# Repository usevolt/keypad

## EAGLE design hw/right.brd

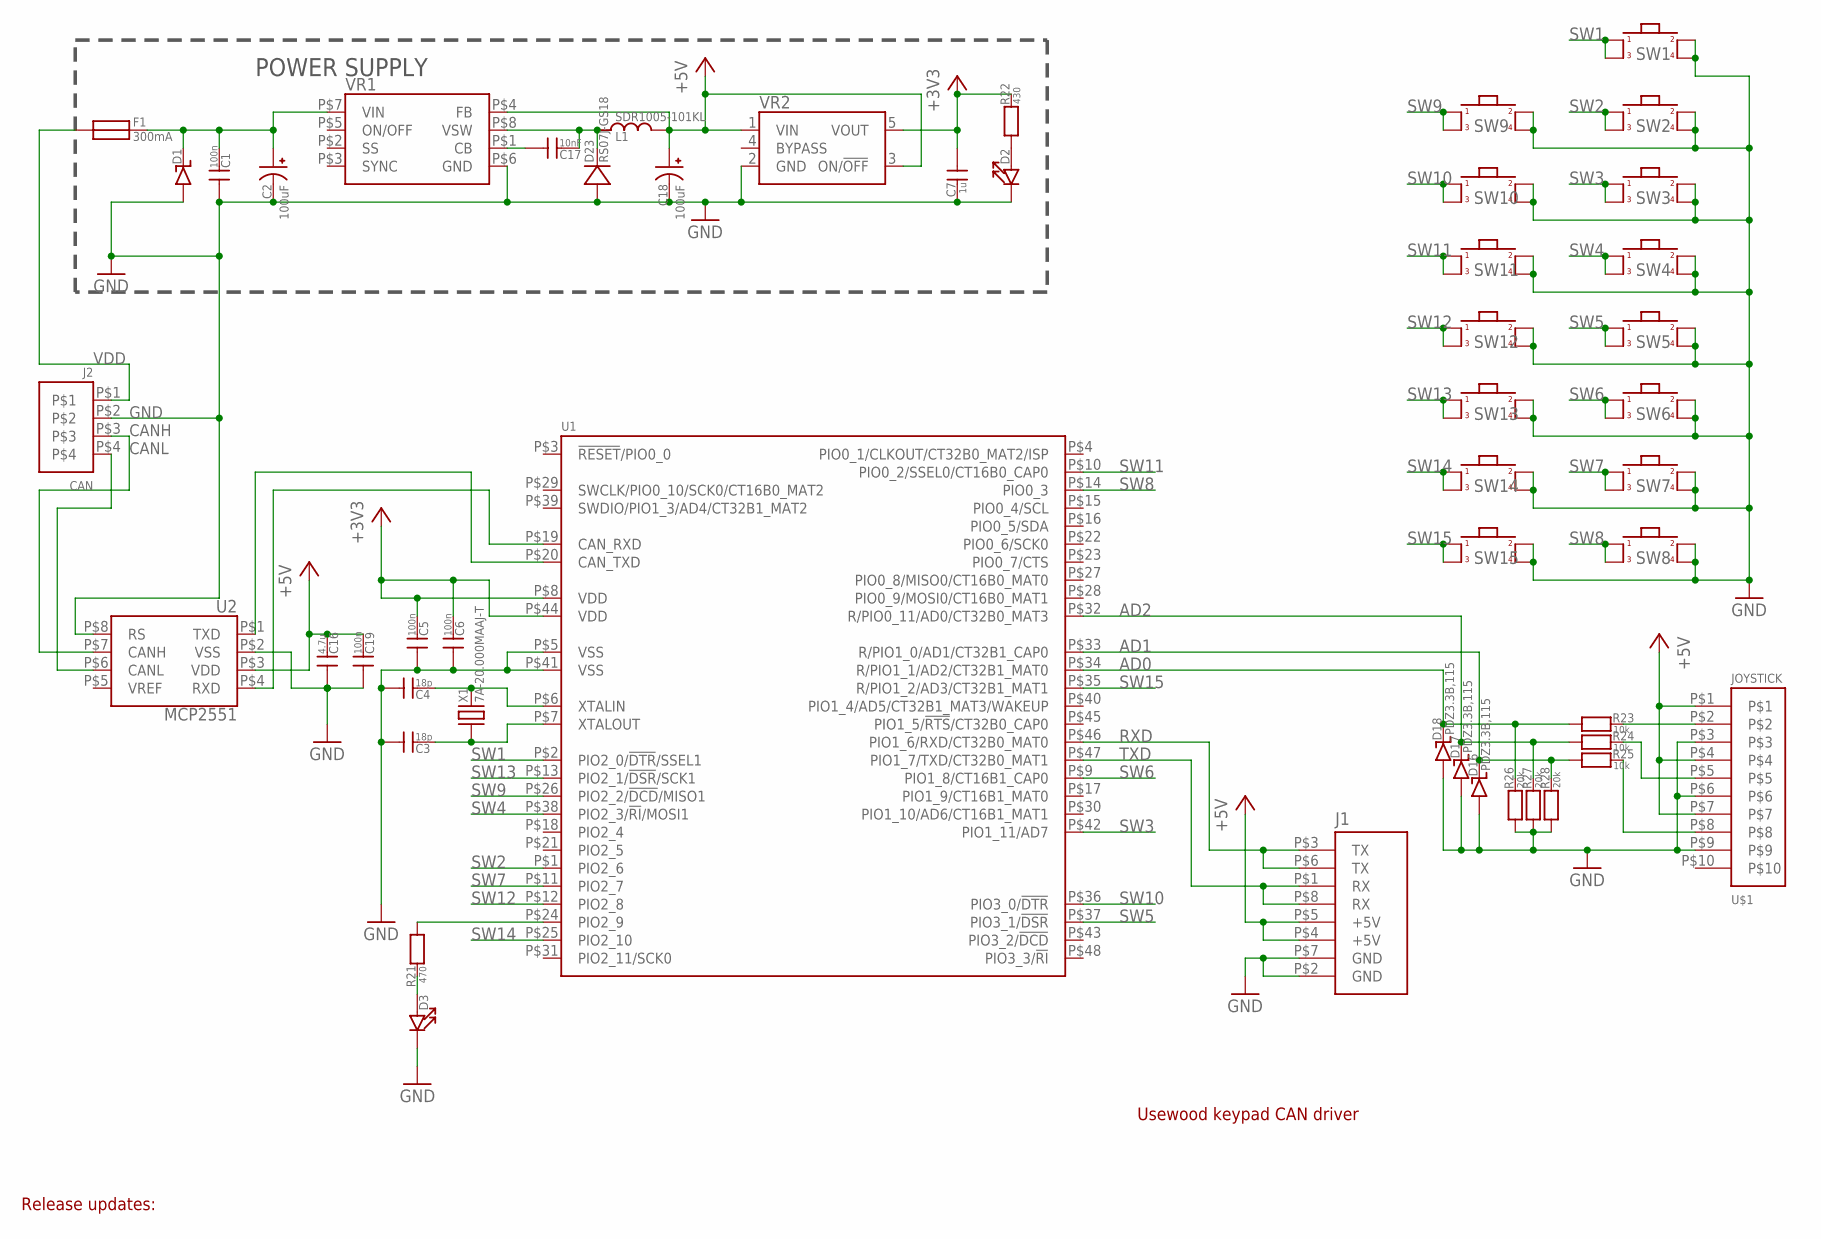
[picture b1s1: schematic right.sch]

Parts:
C1, C5, C6, C19: 100n; 0603_SILKSCREEN
C2, C18: 100uF; CAP_POL_SMD_10X10X10MM
C3, C4: 18p; 0603_SILKSCREEN
C7: 1u; 0603_SILKSCREEN
C16: 4.7u; 0603_SILKSCREEN
C17: 10nF; 0603_SILKSCREEN
D1: DIODE_TVS_SMBJ33A-TRDO-214AA; DO-214AA
D2, D3: LED_0603; 0603_SILKSCREEN
D16, D17, D18: PDZ3.3B,115; SOD123
D23: RS07J-GS18; DO219AB
F1: 300mA; FUSE_100MA
J1: HEADER_USART_2_SMD; HEADER_4_2_SMD
J2: CAN; MOLEX_MICRO_FIT_4WAY_SMD
L1: SDR1005-101KL; INDUCTOR_BOURNS_10X13X5MM
R21: 470; 0603_SILKSCREEN
R22: 430; 0603_SILKSCREEN
R23, R24, R25: 10k; 0603_SILKSCREEN
R26, R27, R28: 20k; 0603_SILKSCREEN
SW1, SW2, SW3, SW4, SW5, SW6, SW7, SW8, SW9, SW10, SW11, SW12, SW13, SW14, SW15: SWITCH_KMR231G; SWITCH_KMR231
U1: LPC11C14_QFP48; QFP48
U2: MCP2551; SOIC8
U$1: JOYSTICK; MOLEX-MICRO-FIT_10WAY
VR1: LM2671SOIC8; SOIC8
VR2: REG_LP2985_SOP5; SOP5
X1: 7A-20.000MAAJ-T; XTAL_SMD_5X3.2

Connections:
+3V3: C5.1, C6.1, C7.0, R22.1, U1.P$8 (VDD), U1.P$44 (VDD), VR2.5 (VOUT)
+5V: C16.1, C18.+, C19.1, J1.P$4 (+5V), J1.P$5 (+5V), L1.P$2, U2.P$3 (VDD), U$1.P$1, U$1.P$4, U$1.P$7, VR1.P$4 (FB), VR2.1 (VIN), VR2.3 (ON/!OFF)
AD0: D18.P$2 (N), R23.0, R26.1, U1.P$34 (R/PIO1_1/AD2/CT32B1_MAT0)
AD1: D16.P$2 (N), R25.0, R28.1, U1.P$33 (R/PIO1_0/AD1/CT32B1_CAP0)
AD2: D17.P$2 (N), R24.0, R27.1, U1.P$32 (R/PIO0_11/AD0/CT32B0_MAT3)
CANH: J2.P$3, U2.P$7 (CANH)
CANL: J2.P$4, U2.P$6 (CANL)
GND: C1.0, C2.-, C3.0, C4.0, C5.0, C6.0, C7.1, C16.0, C18.-, C19.0, D1.P$1, D2.1, D3.1, D16.P$1, D17.P$1, D18.P$1, D23.P$1, J1.P$2 (GND), J1.P$7 (GND), J2.P$2, R26.0, R27.0, R28.0, SW1.P$2, SW1.P$4, SW2.P$2, SW2.P$4, SW3.P$2, SW3.P$4, SW4.P$2, SW4.P$4, SW5.P$2, SW5.P$4, SW6.P$2, SW6.P$4, SW7.P$2, SW7.P$4, SW8.P$2, SW8.P$4, SW9.P$2, SW9.P$4, SW10.P$2, SW10.P$4, SW11.P$2, SW11.P$4, SW12.P$2, SW12.P$4, SW13.P$2, SW13.P$4, SW14.P$2, SW14.P$4, SW15.P$2, SW15.P$4, U1.P$5 (VSS), U1.P$41 (VSS), U2.P$2 (VSS), U2.P$8 (RS), U$1.P$3, U$1.P$6, U$1.P$9, VR1.P$6 (GND), VR2.2 (GND)
LED3: D3.0, R21.1
unnamed: R21.0, U1.P$24 (PIO2_9)
unnamed: D2.0, R22.0
unnamed: C1.1, C2.+, D1.P$2 (N), F1.P$2, VR1.P$7 (VIN)
unnamed: U1.P$20 (CAN_TXD), U2.P$1 (TXD)
unnamed: C17.1, D23.P$2 (N), L1.P$1, VR1.P$8 (VSW)
unnamed: U1.P$19 (CAN_RXD), U2.P$4 (RXD)
unnamed: C17.0, VR1.P$1 (CB)
RXD: J1.P$3 (TX), J1.P$6 (TX), U1.P$46 (PIO1_6/RXD/CT32B0_MAT0)
SW1: SW1.P$1, SW1.P$3, U1.P$2 (PIO2_0/!DTR!/SSEL1)
SW2: SW2.P$1, SW2.P$3, U1.P$1 (PIO2_6)
SW3: SW3.P$1, SW3.P$3, U1.P$42 (PIO1_11/AD7)
SW4: SW4.P$1, SW4.P$3, U1.P$38 (PIO2_3/!RI!/MOSI1)
SW5: SW5.P$1, SW5.P$3, U1.P$37 (PIO3_1/!DSR)
SW6: SW6.P$1, SW6.P$3, U1.P$9 (PIO1_8/CT16B1_CAP0)
SW7: SW7.P$1, SW7.P$3, U1.P$11 (PIO2_7)
SW8: SW8.P$1, SW8.P$3, U1.P$14 (PIO0_3)
SW9: SW9.P$1, SW9.P$3, U1.P$26 (PIO2_2/!DCD!/MISO1)
SW10: SW10.P$1, SW10.P$3, U1.P$36 (PIO3_0/!DTR)
SW11: SW11.P$1, SW11.P$3, U1.P$10 (PIO0_2/SSEL0/CT16B0_CAP0)
SW12: SW12.P$1, SW12.P$3, U1.P$12 (PIO2_8)
SW13: SW13.P$1, SW13.P$3, U1.P$13 (PIO2_1/!DSR!/SCK1)
SW14: SW14.P$1, SW14.P$3, U1.P$25 (PIO2_10)
SW15: SW15.P$1, SW15.P$3, U1.P$35 (R/PIO1_2/AD3/CT32B1_MAT1)
TXD: J1.P$1 (RX), J1.P$8 (RX), U1.P$47 (PIO1_7/TXD/CT32B0_MAT1)
VDD: F1.P$1, J2.P$1
XJOY: R23.1, U$1.P$2
XTALIN: C4.1, U1.P$6 (XTALIN), X1.P$2
XTALOUT: C3.1, U1.P$7 (XTALOUT), X1.P$1
YJOY: R24.1, U$1.P$5
ZJOY: R25.1, U$1.P$8

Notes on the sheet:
Usewood keypad CAN driver
POWER SUPPLY
Release updates:

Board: 2 copper layers, 51 parts (36 on the bottom side), 39 nets, no tracks yet.

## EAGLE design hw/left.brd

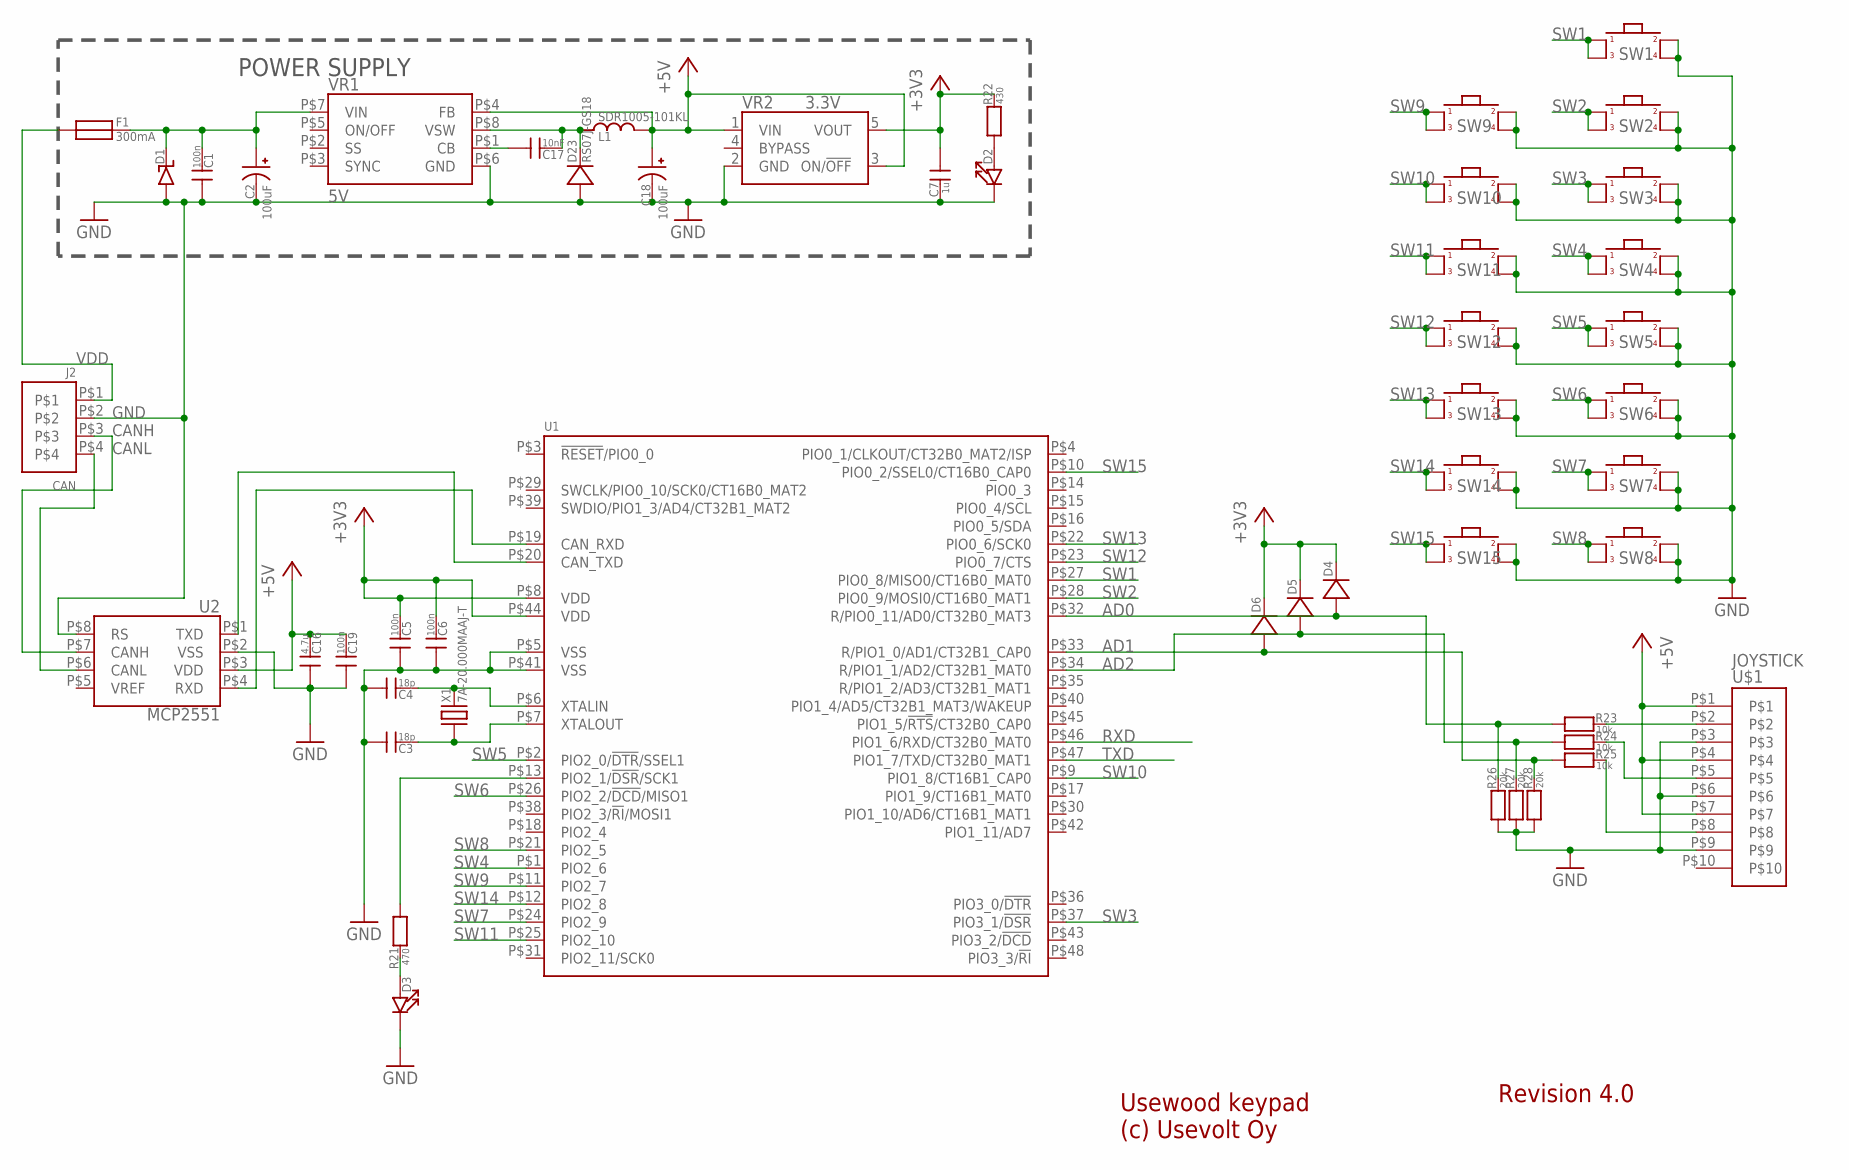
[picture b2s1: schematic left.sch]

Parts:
C1, C5, C6, C19: 100n; 0603_SILKSCREEN
C2, C18: 100uF; CAP_POL_8.3X8.3MM
C3, C4: 18p; 0603_SILKSCREEN
C7: 1u; 0603_SILKSCREEN
C16: 4.7u; 0603_SILKSCREEN
C17: 10nF; 0603_SILKSCREEN
D1: DIODE_TVS_SMBJ33A-TRDO-214AA; DO-214AA
D2, D3: LED_0603; 0603_SILKSCREEN
D4, D5, D6: DIODEDO219AB; DO219AB
D23: RS07J-GS18; DO219AB
F1: 300mA; FUSE_100MA
J2: CAN; MOLEX_MICRO_FIT_4WAY_SMD
L1: SDR1005-101KL; INDUCTOR_BOURNS_10X13X5MM
R21: 470; 0603_SILKSCREEN
R22: 430; 0603_SILKSCREEN
R23, R24, R25: 10k; 0603_SILKSCREEN
R26, R27, R28: 20k; 0603_SILKSCREEN
SW1, SW2, SW3, SW4, SW5, SW6, SW7, SW8, SW9, SW10, SW11, SW12, SW13, SW14, SW15: SWITCH_KSC421J-70SH-LFS
U1: LPC11C14_QFP48; QFP48
U2: MCP2551; SOIC8
U$1: JOYSTICK; MOLEX_MICRO-FIT_10WAY_V
VR1: 5V; SOIC8
VR2: 3.3V; SOP5
X1: 7A-20.000MAAJ-T; XTAL_SMD_5X3.2

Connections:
+3V3: C5.1, C6.1, C7.0, D4.P$2 (N), D5.P$2 (N), D6.P$2 (N), R22.1, U1.P$8 (VDD), U1.P$44 (VDD), VR2.5 (VOUT)
+5V: C16.1, C18.P$2 (+), C19.1, L1.P$2, U2.P$3 (VDD), U$1.P$1, U$1.P$4, U$1.P$7, VR1.P$4 (FB), VR2.1 (VIN), VR2.3 (ON/!OFF)
AD0: D4.P$1, R23.0, R26.1, U1.P$32 (R/PIO0_11/AD0/CT32B0_MAT3)
AD1: D6.P$1, R25.0, R28.1, U1.P$33 (R/PIO1_0/AD1/CT32B1_CAP0)
AD2: D5.P$1, R24.0, R27.1, U1.P$34 (R/PIO1_1/AD2/CT32B1_MAT0)
CANH: J2.P$3, U2.P$7 (CANH)
CANL: J2.P$4, U2.P$6 (CANL)
GND: C1.0, C2.P$1 (-), C3.0, C4.0, C5.0, C6.0, C7.1, C16.0, C18.P$1 (-), C19.0, D1.P$1, D2.1, D3.1, D23.P$1, J2.P$2, R26.0, R27.0, R28.0, SW1.P$3, SW1.P$4, SW2.P$3, SW2.P$4, SW3.P$3, SW3.P$4, SW4.P$3, SW4.P$4, SW5.P$3, SW5.P$4, SW6.P$3, SW6.P$4, SW7.P$3, SW7.P$4, SW8.P$3, SW8.P$4, SW9.P$3, SW9.P$4, SW10.P$3, SW10.P$4, SW11.P$3, SW11.P$4, SW12.P$3, SW12.P$4, SW13.P$3, SW13.P$4, SW14.P$3, SW14.P$4, SW15.P$3, SW15.P$4, U1.P$5 (VSS), U1.P$41 (VSS), U2.P$2 (VSS), U2.P$8 (RS), U$1.P$3, U$1.P$6, U$1.P$9, VR1.P$6 (GND), VR2.2 (GND)
LED3: D3.0, R21.1
unnamed: R21.0, U1.P$13 (PIO2_1/!DSR!/SCK1)
unnamed: D2.0, R22.0
unnamed: C1.1, C2.P$2 (+), D1.P$2 (N), F1.P$2, VR1.P$7 (VIN)
unnamed: U1.P$20 (CAN_TXD), U2.P$1 (TXD)
unnamed: C17.1, D23.P$2 (N), L1.P$1, VR1.P$8 (VSW)
unnamed: U1.P$19 (CAN_RXD), U2.P$4 (RXD)
unnamed: C17.0, VR1.P$1 (CB)
RXD: U1.P$46 (PIO1_6/RXD/CT32B0_MAT0)
SW1: SW1.P$1, SW1.P$2, U1.P$27 (PIO0_8/MISO0/CT16B0_MAT0)
SW2: SW2.P$1, SW2.P$2, U1.P$28 (PIO0_9/MOSI0/CT16B0_MAT1)
SW3: SW3.P$1, SW3.P$2, U1.P$37 (PIO3_1/!DSR)
SW4: SW4.P$1, SW4.P$2, U1.P$1 (PIO2_6)
SW5: SW5.P$1, SW5.P$2, U1.P$2 (PIO2_0/!DTR!/SSEL1)
SW6: SW6.P$1, SW6.P$2, U1.P$26 (PIO2_2/!DCD!/MISO1)
SW7: SW7.P$1, SW7.P$2, U1.P$24 (PIO2_9)
SW8: SW8.P$1, SW8.P$2, U1.P$21 (PIO2_5)
SW9: SW9.P$1, SW9.P$2, U1.P$11 (PIO2_7)
SW10: SW10.P$1, SW10.P$2, U1.P$9 (PIO1_8/CT16B1_CAP0)
SW11: SW11.P$1, SW11.P$2, U1.P$25 (PIO2_10)
SW12: SW12.P$1, SW12.P$2, U1.P$23 (PIO0_7/CTS)
SW13: SW13.P$1, SW13.P$2, U1.P$22 (PIO0_6/SCK0)
SW14: SW14.P$1, SW14.P$2, U1.P$12 (PIO2_8)
SW15: SW15.P$1, SW15.P$2, U1.P$10 (PIO0_2/SSEL0/CT16B0_CAP0)
TXD: U1.P$47 (PIO1_7/TXD/CT32B0_MAT1)
VDD: F1.P$1, J2.P$1
XJOY: R23.1, U$1.P$2
XTALIN: C4.1, U1.P$6 (XTALIN), X1.P$2
XTALOUT: C3.1, U1.P$7 (XTALOUT), X1.P$1
YJOY: R24.1, U$1.P$5
ZJOY: R25.1, U$1.P$8

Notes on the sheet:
Usewood keypad (c) Usevolt Oy
POWER SUPPLY
Revision 4.0

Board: 2 copper layers, 50 parts (1 on the bottom side), 37 nets, no tracks yet.

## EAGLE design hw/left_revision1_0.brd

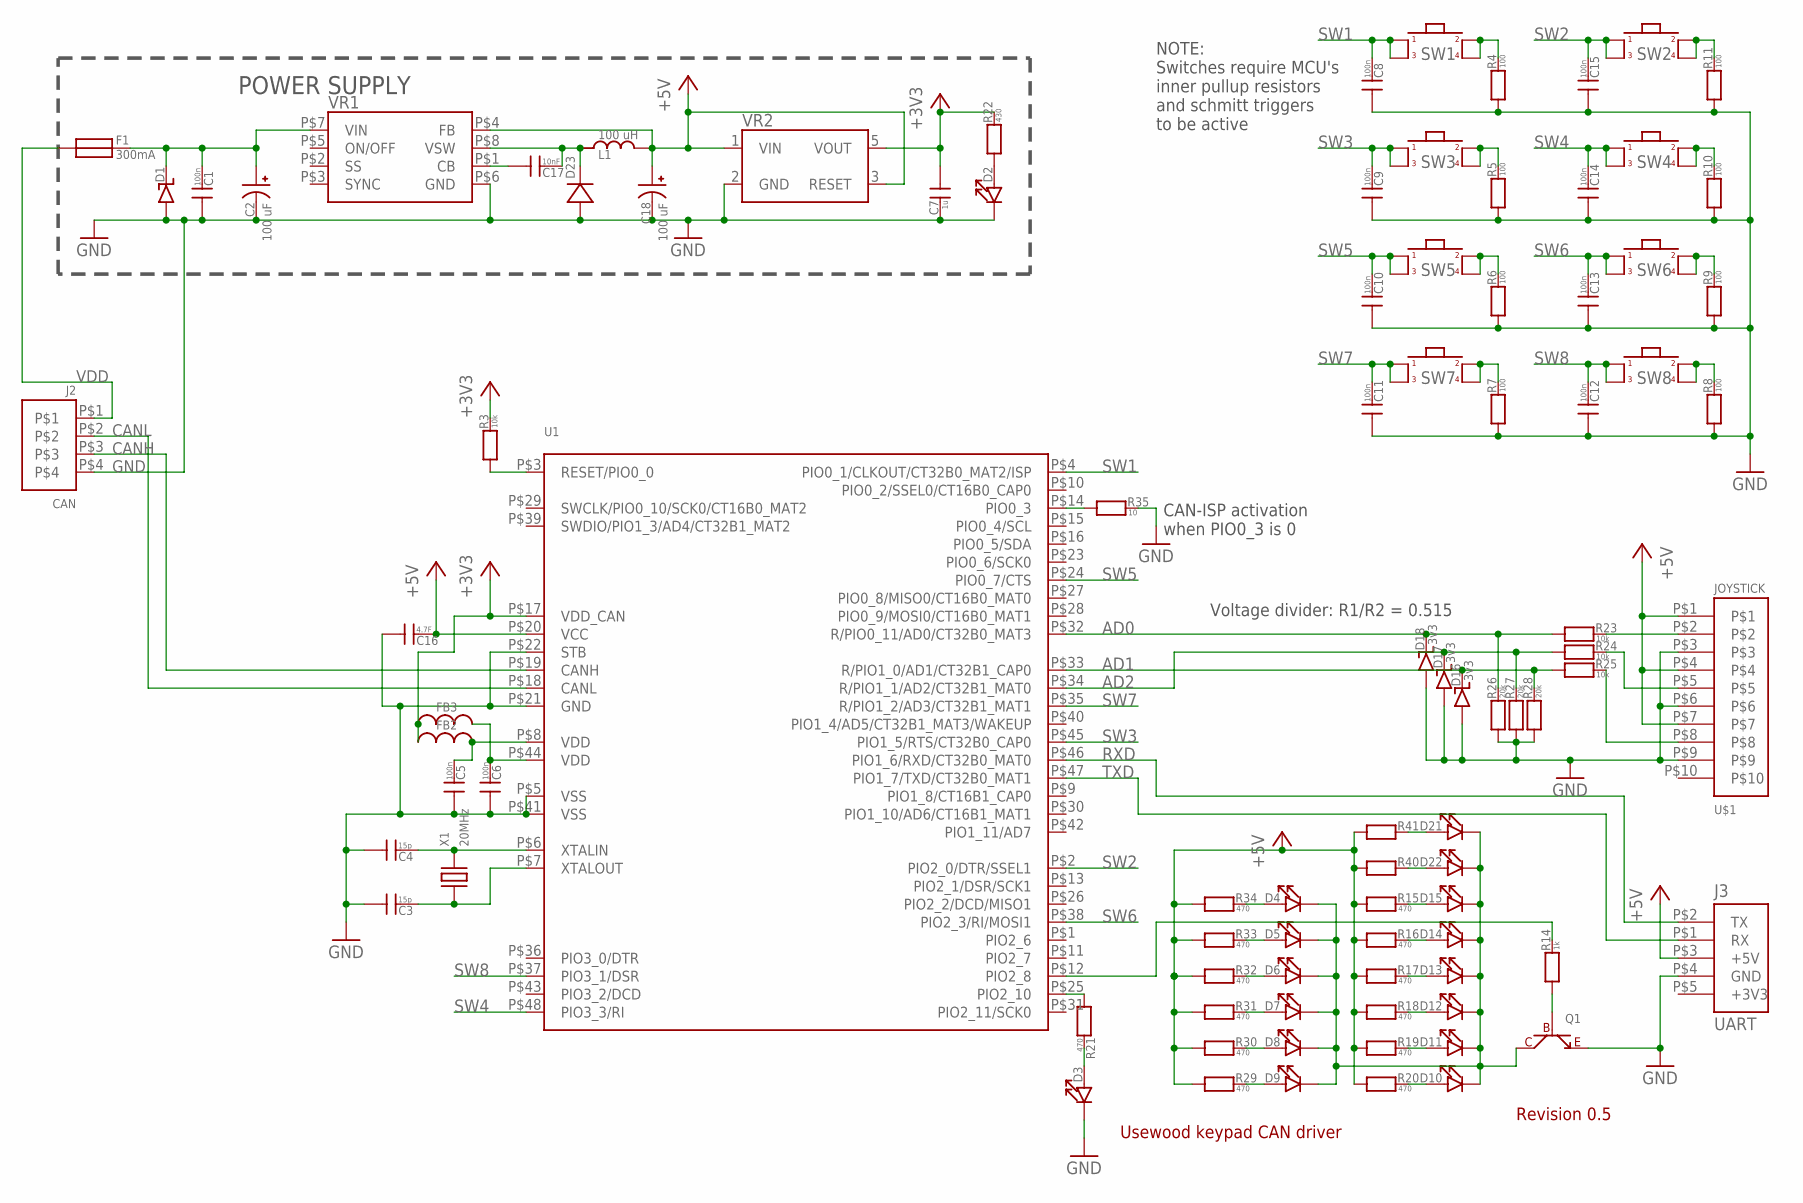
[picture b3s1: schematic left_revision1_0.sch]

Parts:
C1, C5, C6, C8, C9, C10, C11, C12, C13, C14, C15: 100n; 0603_SILKSCREEN
C2, C18: 100 uF; CAP_POL_SMD_10X10X10MM
C3, C4: 15p; 0603_SILKSCREEN
C7: 1u; 0603_SILKSCREEN
C16: 4.7F; 0603_SILKSCREEN
C17: 10nF; 0603_SILKSCREEN
D1: DIODE_TVSDO-214AA; DO-214AB
D2, D3, D4, D5, D6, D7, D8, D9, D10, D11, D12, D13, D14, D15, D21, D22: LED0603_SILKSCREEN; 0603_SILKSCREEN
D16, D17, D18: 3v3; SOD123
D23: DIODEDO219AB; DO219AB
F1: 300mA; FUSE_100MA
FB2, FB3: FERRITE0603_SILKSCREEN; 0603_SILKSCREEN
J2: CAN; MOLEX_MICRO-FIT_4WAY
J3: UART; HEADER5_1
L1: 100 uH; INDUCTOR_BOURNS_10X13X5MM
Q1: NPN_TRANSISTORSOT323; SOT323
R3, R23, R24, R25: 10k; 0603_SILKSCREEN
R4, R5, R6, R7, R8, R9, R10, R11: 100; 0603_SILKSCREEN
R14: 1k; 0603_SILKSCREEN
R15, R16, R17, R18, R19, R20, R21, R29, R30, R31, R32, R33, R34: 470; 0603_SILKSCREEN
R22: 430; 0603_SILKSCREEN
R26, R27, R28: 20k; 0603_SILKSCREEN
R35: 10; 0603_SILKSCREEN
R40, R41: RES0604_SILKSCREEN; 0603_SILKSCREEN
SW1, SW2, SW3, SW4, SW5, SW6, SW7, SW8: SWITCH12X12MM_CENTER_HOLE; SWITCH_12X12MM_CENTER_HOLE
U1: LPC11C22QFP48; QFP48
U$1: JOYSTICK; MOLEX-MICRO-FIT_10WAY
VR1: LM2671SOIC8; SOIC8
VR2: LP2985SOP5; SOP5
X1: 20MHz; XTAL_SMD_5X3.2

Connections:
+3V3: C7.0, FB2.0, FB3.0, R3.1, R22.1, U1.P$17 (VDD_CAN), VR2.5 (VOUT)
+5V: C16.1, C18.+, J3.P$3 (+5V), L1.P$2, R15.0, R16.0, R17.0, R18.0, R19.0, R20.0, R29.0, R30.0, R31.0, R32.0, R33.0, R34.0, R40.0, R41.0, U1.P$20 (VCC), U$1.P$1, U$1.P$4, U$1.P$7, VR1.P$4 (FB), VR2.1 (VIN), VR2.3 (RESET)
AD0: D18.P$2 (N), R23.0, R26.1, U1.P$32 (R/PIO0_11/AD0/CT32B0_MAT3)
AD1: D16.P$2 (N), R25.0, R28.1, U1.P$33 (R/PIO1_0/AD1/CT32B1_CAP0)
AD2: D17.P$2 (N), R24.0, R27.1, U1.P$34 (R/PIO1_1/AD2/CT32B1_MAT0)
CANH: J2.P$3, U1.P$19 (CANH)
CANL: J2.P$2, U1.P$18 (CANL)
CAN_ISP: R35.0, U1.P$14 (PIO0_3)
GND: C1.0, C2.-, C3.0, C4.0, C5.0, C6.0, C7.1, C8.0, C9.0, C10.0, C11.0, C12.0, C13.0, C14.0, C15.0, C16.0, C18.-, D1.P$1, D2.1, D3.1, D16.P$1, D17.P$1, D18.P$1, D23.P$1, J2.P$4, J3.P$4 (GND), Q1.R (E), R4.0, R5.0, R6.0, R7.0, R8.0, R9.0, R10.0, R11.0, R26.0, R27.0, R28.0, R35.1, U1.P$5 (VSS), U1.P$21 (GND), U1.P$22 (STB), U1.P$41 (VSS), U$1.P$3, U$1.P$6, U$1.P$9, VR1.P$6 (GND), VR2.2 (GND)
LED3: D3.0, R21.1
LED4: D4.0, R34.1
LED5: D5.0, R33.1
LED6: D6.0, R32.1
LED7: D7.0, R31.1
LED8: D8.0, R30.1
LED9: D9.0, R29.1
unnamed: C6.1, FB3.1, U1.P$44 (VDD)
unnamed: D2.0, R22.0
unnamed: C1.1, C2.+, D1.P$2 (N), F1.P$2, VR1.P$7 (VIN)
unnamed: R14.1, U1.P$12 (PIO2_8)
unnamed: R21.0, U1.P$25 (PIO2_10)
unnamed: C17.1, D23.P$2 (N), L1.P$1, VR1.P$8 (VSW)
unnamed: R4.1, SW1.P$3, SW1.P$4
unnamed: R5.1, SW3.P$3, SW3.P$4
unnamed: R6.1, SW5.P$3, SW5.P$4
unnamed: R11.1, SW2.P$3, SW2.P$4
unnamed: R9.1, SW6.P$3, SW6.P$4
unnamed: R10.1, SW4.P$3, SW4.P$4
unnamed: R8.1, SW8.P$3, SW8.P$4
unnamed: R7.1, SW7.P$3, SW7.P$4
unnamed: D15.0, R15.1
unnamed: D14.0, R16.1
unnamed: D13.0, R17.1
unnamed: D12.0, R18.1
unnamed: D11.0, R19.1
unnamed: D10.0, R20.1
unnamed: C5.1, FB2.1, U1.P$8 (VDD)
unnamed: D21.0, R41.1
unnamed: D22.0, R40.1
unnamed: D4.1, D5.1, D6.1, D7.1, D8.1, D9.1, D10.1, D11.1, D12.1, D13.1, D14.1, D15.1, D21.1, D22.1, Q1.M (C)
unnamed: C17.0, VR1.P$1 (CB)
Q1: Q1.L (B), R14.0
RESET: R3.0, U1.P$3 (RESET/PIO0_0)
RXD: J3.P$2 (TX), U1.P$46 (PIO1_6/RXD/CT32B0_MAT0)
SW1: C8.1, SW1.P$1, SW1.P$2, U1.P$4 (PIO0_1/CLKOUT/CT32B0_MAT2/ISP)
SW2: C15.1, SW2.P$1, SW2.P$2, U1.P$2 (PIO2_0/DTR/SSEL1)
SW3: C9.1, SW3.P$1, SW3.P$2, U1.P$45 (PIO1_5/RTS/CT32B0_CAP0)
SW4: C14.1, SW4.P$1, SW4.P$2, U1.P$48 (PIO3_3/RI)
SW5: C10.1, SW5.P$1, SW5.P$2, U1.P$24 (PIO0_7/CTS)
SW6: C13.1, SW6.P$1, SW6.P$2, U1.P$38 (PIO2_3/RI/MOSI1)
SW7: C11.1, SW7.P$1, SW7.P$2, U1.P$35 (R/PIO1_2/AD3/CT32B1_MAT1)
SW8: C12.1, SW8.P$1, SW8.P$2, U1.P$37 (PIO3_1/DSR)
TXD: J3.P$1 (RX), U1.P$47 (PIO1_7/TXD/CT32B0_MAT1)
VDD: F1.P$1, J2.P$1
XJOY: R23.1, U$1.P$2
XTALIN: C4.1, U1.P$6 (XTALIN), X1.P$2
XTALOUT: C3.1, U1.P$7 (XTALOUT), X1.P$1
YJOY: R24.1, U$1.P$5
ZJOY: R25.1, U$1.P$8

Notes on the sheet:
Usewood keypad CAN driver
Revision 0.5
Voltage divider: R1/R2 = 0.515
NOTE: Switches require MCU's inner pullup resistors and schmitt triggers to be active
CAN-ISP activation when PIO0_3 is 0
POWER SUPPLY

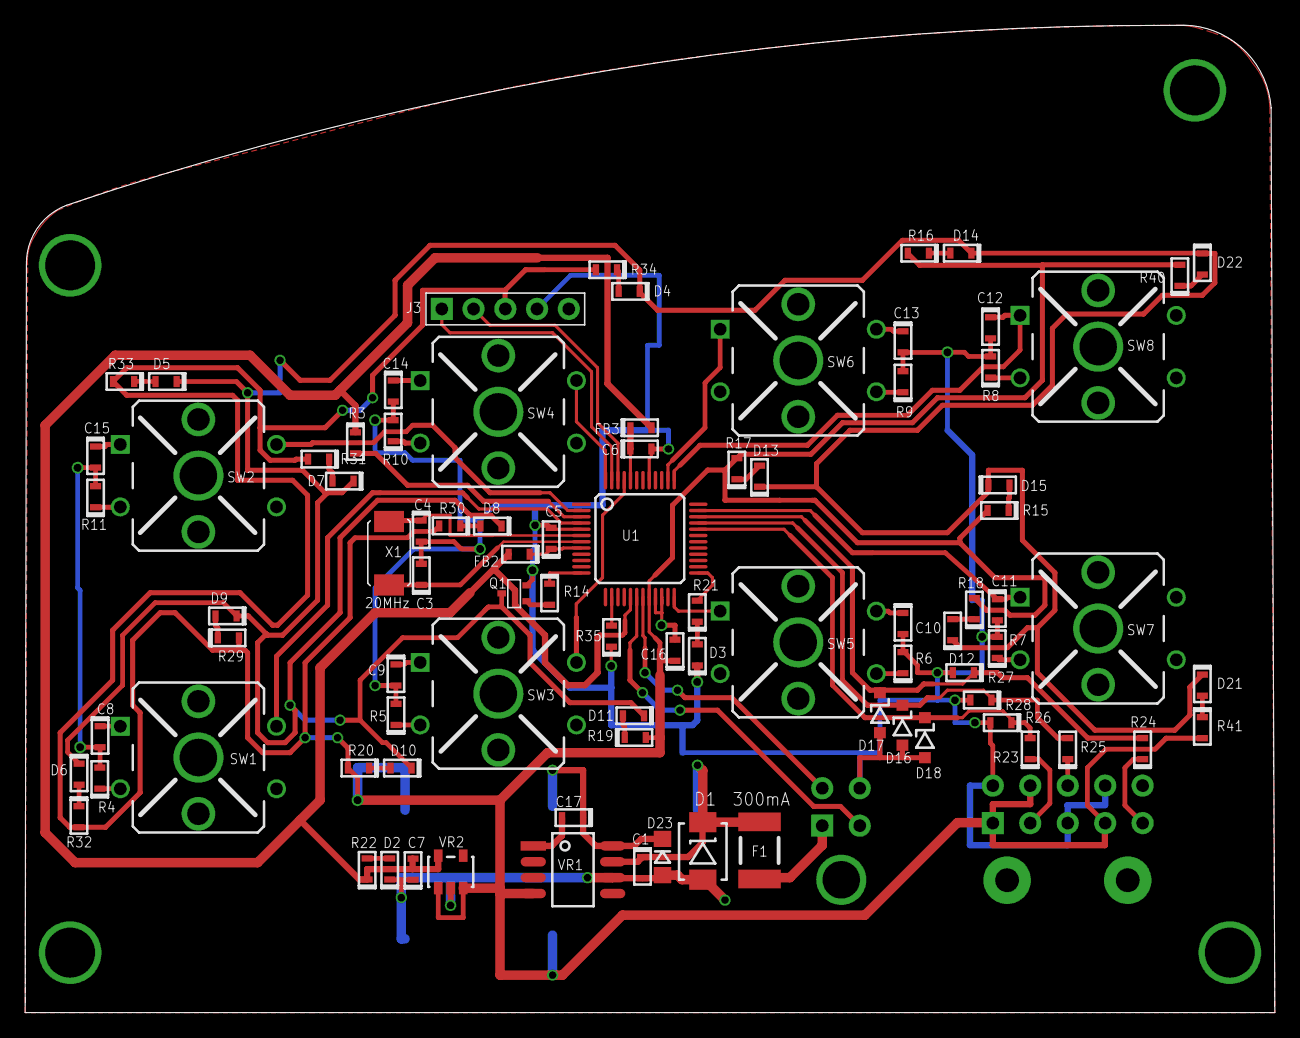
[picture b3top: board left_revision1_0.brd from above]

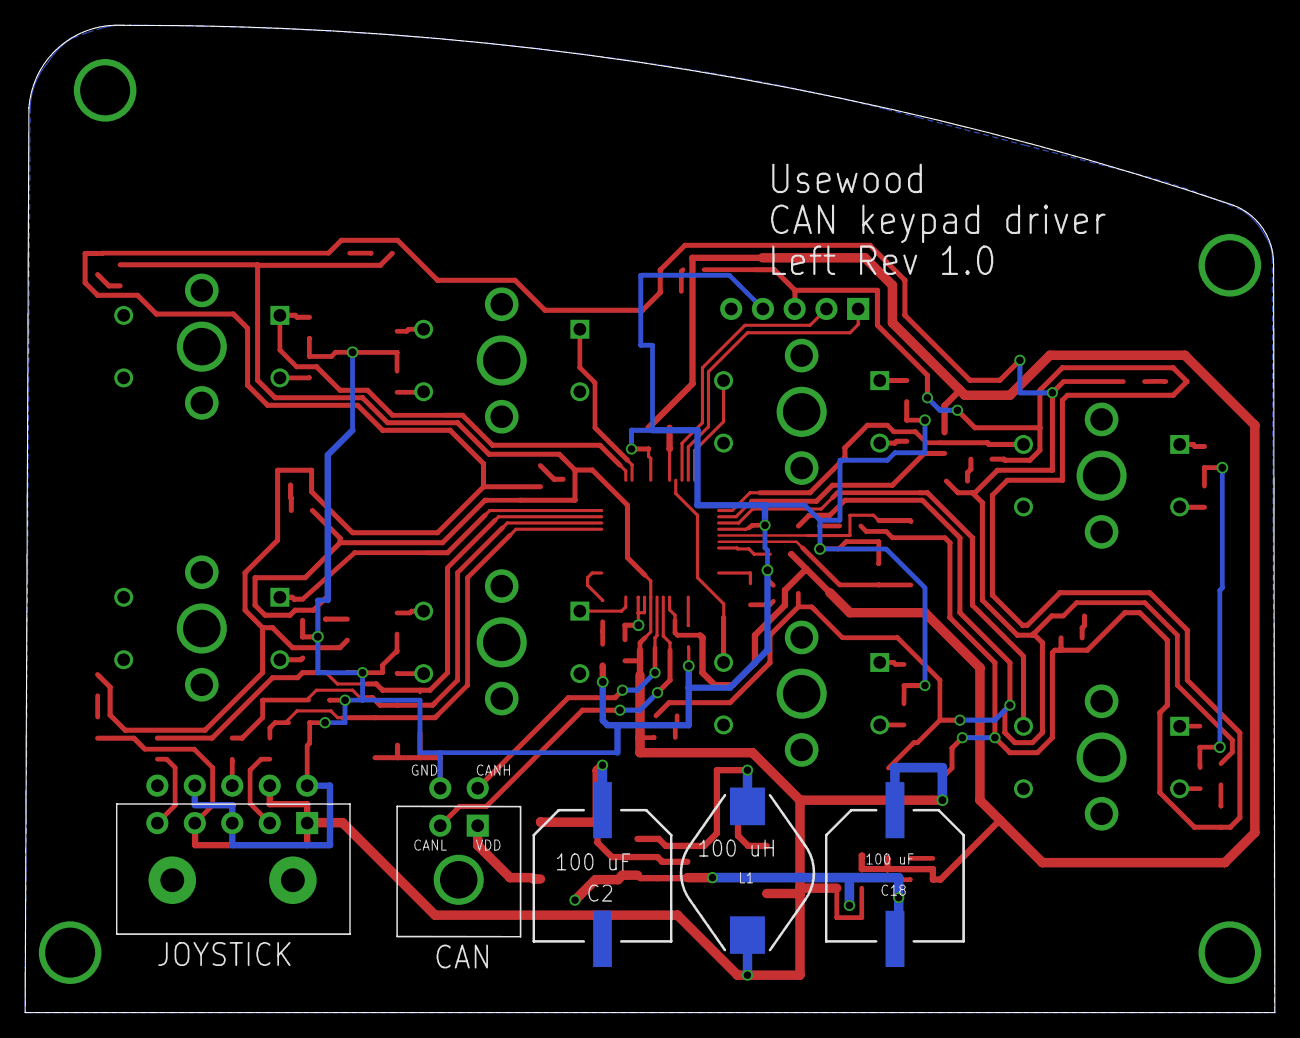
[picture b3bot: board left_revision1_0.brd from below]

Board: 2 copper layers, 100.0 x 79.0 mm, 92 parts (5 on the bottom side), 59 nets.

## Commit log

2016-02-23 Add initial SW and HW files
    - copy sw & hw versions 0.5, 1.0 & 1.1 from svn version control
    - change hal library paths to point into LPC11C14 in version_control/hal
2016-03-03 Add 1.0, 1.1 & 1.2 HW versions to version control
    - They were missing from last commit
2016-03-28 Add 2.0 and 3.0 HW versions
2016-04-30 version 3.0 hardware drawn
2016-05-18 Keypad files modified to use build-time configurable uw_hal library
2016-05-18 Deleted old HW revision files
2016-06-16 HW revision 3.0
2016-06-19 developing HW version 4.0
2016-07-04 implementing the next version of HW
2016-07-04 hal library changed from uw to uv
2016-09-08 Designing the kicad version of hw
2016-10-24 revision 5 ordered from itead
2016-12-22 implementing firmware for 5.0 hw
2017-01-04 Added .gitmodules for hal submodule
2017-01-04 binary files removed from repo
2017-01-04 gitmodules removed
2017-01-04 HAL submodule included in the version control
2017-01-04 tx buffer updated to CAN hal
2017-01-04 deleted object files
2017-01-04 makefile .map moved to object directory
2017-01-25 Created covers and ordered them from shapeways
2017-02-08 ordupdated enclosures to have 4 round buttons instead of 2 switches
2017-03-10 not working version with renewed object dictionary interface
2017-03-11 pcb hw revision 5 software with new obj dict interface
2017-03-28 hw but 5 & 6 rotated 20 degrees to fit their places
2017-03-31 axis calibration available only if axis has no active error
2017-04-01 screw hole pocket radius increased
2017-04-04 axis calibration min & max value added threshold
    Hopefully reduced hazards, since min cannot be greater or equal to middle value, same for max.
2017-04-11 bug fix: Axis calib msb obj's array length corrected
2017-05-18 enclosure bug fixes:
    2 outermost button's rotation corrected
    cover's border thickness increased for good 3d print manufacturing
2017-06-27 enclosure plane thickness is now constant 1.0 mm
2017-07-10 added OTTO JHM model and created assembly file
2017-07-12 version 3 top collar ordered from shapeways
2017-12-17 drawing right2 pcb
2018-08-27 sw compiles without dependencies to lpcxpresso
2018-08-27 button count reduced, b5, 6, 7 grouped together
2019-01-26 stencil gerbers created from old keypads
2019-06-02 button plastics updated to imaterialise ordering
2019-06-02 keypads can revive from bus off
2019-10-09 submodule urls set to https github
2021-10-26 covers without buttons step and stl created
